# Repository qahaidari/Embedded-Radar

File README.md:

# Embedded-Radar-STMicrocontroller-Cprogramming
Embedded radar sensor circuit with STM32 microcontroller and C programming for measuring target speed

# Skills learned in this project:
* GIT
* Basics of hardware design and PCB layout
* Digital and analog circuits
* Accessing peripheral components
* Interrupts, serial I/O, general purpose I/O, ...
* RTOS, multitasking, synchronization, semaphores
* STM32CubeMx configuration code generator
* Schematic CAD software (KiCAD Eeschema): placing parts, connections in schematic, footprints, annotation, netlist
* PCB CAD software (KiCAD): loading netlist, GND pours, Vias, Gerber and Drill files for production
* Soldering components on PCB
* IDE Atollic TrueSTUDIO (Eclipse)
* C programming
* Configuring switches as external interrupts
* Communication between Interrupt Service Routine (ISR) and queue
* Configuring and using ADC
* Configuring and using timers
* Configuring LEDs
* Interfacing with LCD

# Project Description

## Introduction

RADAR stands for Radio Detection And Ranging and is a detection system that uses radio waves to determine the range, angle, or velocity of objects. It can be used to detect aircraft, ships, spacecraft, guided missiles, motor vehicles, weather formations, and terrain. Radars are now involved in various applications. It was initially used for target detection in military applications but nowadays it is used in tracking of aircrafts and vehicles and also in traffic control and space. In this project we will concentrate on motion and speed detection of objects using Radars.

The basic concept of Radar is sending an electromagnetic signal from a source which is radiating in the space. This signal will hit a moving object and then be reflected back to the source. In our case, the transmitter and receiver are on the same board of the radar device. The reflected signal from the object will be processed in the device and then finally sent to a microcontroller where the speed of the moving object is calculated using the Doppler effect.

The Doppler effect is the change of the frequency of an incident wave on a moving object in its reflected wave. The difference in frequencies is measured through a microcontroller to measure the speed of the moving object using the below formulas:

where  is the difference between transmitted and received frequencies of the signal,  is the wavelength,  is the frequency of the transmitted signal,  is the speed of light and  is the velocity of the object.

## Hardware Setup

### Circuit Design and Components

In this project, we are using an input source for the signal generation and reception, an amplifier and filter stage, a processing unit, a display, two switches and three LEDs. Below figure shows the block diagram of the project.

In the first stage, we use an IPM-165 Radar module which contains a full duplex patch antenna that transmits and receives signals in the K-band (24GHz). The reflected signal from the moving object has a slightly different frequency than that of the transmitted signal. This difference can be detected by the internal oscillator and the mixer inside the Radar module.

In the next stage, we use an amplifier to amplify the received signal for a more precise measurement and in order to increase the ability to detect objects far from the Radar module.

Due to possible additional noise in the environment which would affect the measurements negatively, we have also included a Notch filter that can suppress the noise at a certain frequency. We have included a filter with a 100Hz frequency suppression as we might have neon light in the environment which would produce signals in this range. The drawback is that the respective speeds in the 100Hz frequency range will not be detected. So we are using both a filtered signal and a non-filtered signal in this project.   

In the next stage we use the STM32L476 microcontroller. It converts the analog signal from the Radar module to a digital signal for processing. By processing the sampled digital signal, the microcontroller calculates the signal frequency and the speed of the object using the Doppler formula. The results for both filtered and non-filtered signals will be displayed on the LCD for user reading.

Two switches (one for switching between the filtered and non-filtered signal and one for freezing the maximum speed on the LCD) and three LEDs (for indicating the filtered, non-filtered and freeze states) are used for user requests and status indication.

### Schematic and Hardware Considerations

There are some points that should be considered in the hardware design in addition to the previous main blocks. We will highlight them in this section as shown in the following schematics.

**Power Supply Decoupling Capacitors:** It is highly recommended to connect capacitors to the input DC power supply to minimize the ripples that can be formed due to a non-ideal source. The capacitors C14 to C16 are used at the biasing of operational amplifier, Radar sensor and LCD and the capacitors C12 and C13 are connected to the input power supply. Below figure shows the schematic of decoupling capacitors for main power supply and power supplies of LCD, radar sensor and operational amplifier.

**Operational Amplifier and Notch Filter:** In our design, we used 3 Op-amps, and for size reduction we used a compact IC MC33079 which has 4 Op-amps. The first 2 Op-amps (U1A and U1B) are used in the amplifier circuit stage. The last Op-amp (U1D) is used as a voltage follower to isolate the effect of the load (microcontroller) on the voltage of the connected RC filter at the input of the Op-amp. The Notch filter is used to suppress the effect of noise at 100Hz frequency. Below figure shows the operational amplifier and the Notch filter with their connectivity to the microcontroller. The non-filtered signal is fed to pin PC0 and the filtered signal to pin PC1.

**Switch Buttons:** We used 2 switch buttons that should be connected to a debouncing circuit containing resistors and capacitors so that their bouncing when being pressed is canceled. Below figure shows their connectivity with the microcontroller. We used the formula

to calculate the time , and from it we can calculate the resistor value  from

Taking the bouncing time of the switches as  and the value of capacitor as , we calculated  

<a href="https://www.codecogs.com/eqnedit.php?latex=\large&space;\tau&space;>=&space;2.7(ms)" target="_blank">=&space;2.7(ms)" title="\large \tau >= 2.7(ms)" /></a>

and this gave us

<a href="https://www.codecogs.com/eqnedit.php?latex=\large&space;R&space;>=&space;27(k\Omega)" target="_blank">=&space;27(k\Omega)" title="\large R >= 27(k\Omega)" /></a>

We finally chose the smallest E24 resistor for  and  as . 

Below figure shows the two switches connected to microcontroller.

**LED Indicators:** We used 3 red LEDs for status indication of the measuring process. We need a resistor at each LED to operate them at the desired intensity. According to the data sheet, the voltage drop was calculated using the Kirchoff's voltage law, and the resistors were calculated as .

### Operational Flowchart
 
Below figure represents the flowchart of the Radar operation.

In this project we have considered 2 scales for the calculation of speed: Kilometer per hour and meter per second, both are displayed on the screen. We can distinguish between filtered and non-filtered signals. The user can switch between them by using switch 2 and the respective speeds in kmh and m/s will be displayed on the LCD. Switch 1 is used to freeze the maximum speed which has been captured so far. LED1 will be ON to indicate the freeze state, and LED2 and LED3 will be ON to show if the filtered signal or the nonfiltered signal has been selected respectively.
 
## Software Concept

**Interrupts:** There are two switches (SW1 and SW2) which act as external interrupts. The following external interrupt callback function sends a specific flag to the queue depending on which one has been pressed.

In the main task, anytime the SW2 flag is received from the queue, a switch between measurements for filtered and non-filtered signal will happen. This is done by changing the value of a local variable `state` on each SW2-ISR to Task communication. Depending on the value of `state`, an appropriate channel of ADC which takes samples from either a filtered or a non-filtered signal is selected.

**Global Variables:** The following global variables with their respective initial values have been used in the program:

```c 
int final_count = 0;
```
`final_count` indicates number of samples between two successive zeros in the signal.

```c
int timer_div = 0;
```
```c
int sample = 0, prevsample = 0;
```
```c
sample_count = 0;
```
`sample_count` is incremented each time a new sample is taken.

```c
freeze = 1;
```
```c
double min_final_count = 30000;
```

**Timer Settings for ADC Sampling:** The timer parameters have been set as the following:

```c
Prescaler = 1500;
```
```c
Period = 1;
```
```c
ClockDivision = 4;
```
Since the internal clock for the timer is 80MHz, these settings will make the final timer clock around 13333Hz. During each timer clock, ADC takes a sample and converts it to a digital value. This makes the sampling rate over 20 times the highest frequency (600Hz) in the received signal (Nyquist criterion for sampling an analog signal with at least twice the highest frequency in the signal has been fulfilled).

**Local Variables in the Default Task:**
```c
int cIn = 0;
```
```c
int state = 1;
```
```c
double half_period = 0, doppler_f = 0;
```
```c
double v_kmh = 0, v_ms = 0;
```
```c
char str[10];
```

**Static Local Variable:** The static local variable `OFFSET` is used in the timer service routine function to account for the offset value of the received signal.

**Communication between Timer Service Routine Function and the Task:**

Sending the flag `cIn = 3` from the timer SR to the queue: It is sent to the queue whenever a new zero crossing is detected and the current value of `sample_count` is put into `final_count` indicating the number of samples for the previous half period of the signal. `sample_count` value is then set to zero to start counting the number of samples in a new zero-crossing to zero-crossing interval.

The flag `cIn = 4` is sent to the queue whenever the global variable `timer_div` reaches 4000. `timer_div` is incremented any time a timer clock calls the timer service routine function in which a new sample is taken and counted. This flag is used in order not to refresh the contents on the LCD screen any time a new speed is about to be displayed.

**Functions of Switches and LEDs:**

SW2: Switching between filtered and non-filtered measurements

SW1: Freezing the max speed captured so far on LCD. The default state is not to freeze

LED2: Filtered signal has been selected

LED3: Non-filtered signal has been selected

LED1: Indicating the freeze state

**Freezing the Max Speed on LCD:** The global variable `min_final_count = 30000` is used in combination with the global variable `freeze` to freeze the maximum speed which has been captured so far. Switching between freezing and non-freezing states is done by the flag `cIn = 1` which is received in the default task from the EXTI Callback function.

Anytime a switch between filtered and non-filtered signal happens (through SW2), `min_final_count` is reset to 30000 so that the max speed for the new signal type will not be affected by the values of the last signal type. Also, if this switch happens in the freeze state, the speed values will be reset to zero so that the previous frozen max speeds will not stay on the LCD screen.

In the non-freeze state, whenever a new `final_count` is received (through timer SR to task communication), it is compared with the current `min_final_count` to update it for the max speed in the freeze state. In the freeze state, `min_final_count` is taken for measurements.

## Conclusion

**A Concluding Note on Frequency Calculation:** When a signal is received from the Radar sensor, the calculation will be performed in the processor of the microcontroller. Since the highest signal frequency that is received is 600Hz, the sampling rate according to the Nyquist criteria should be at least double this value. We have adjusted the timer parameters in such a way so that the timer service function is called 13333 times per second and within each call, ADC takes one sample. This makes the sampling rate over 20 times the highest frequency. Whenever one sample is taken, it is compared with its previous sample to detect two successive zero crossings and count the number of samples taken within these zero crossings. Since the time for taking one sample is known based on the sampling rate of the timer/ADC, the half period of the signal can be measured. During this process, an offset value and also a threshold value for canceling the noise have been considered. By knowing the period and frequency of the signal, the speed of the object will be measured using the Doppler formula. 

The user can hold the reading on the LCD screen if switch 1 is pressed which will display the maximum speed calculated since the last reading. LED1 will be on to indicate the hold state. The user can release the hold state by pressing switch 1 again and the system will return again to wait for a new received signal.

# Below figure shows the final PCB with soldered components, mounted on the STMicrocontroller.

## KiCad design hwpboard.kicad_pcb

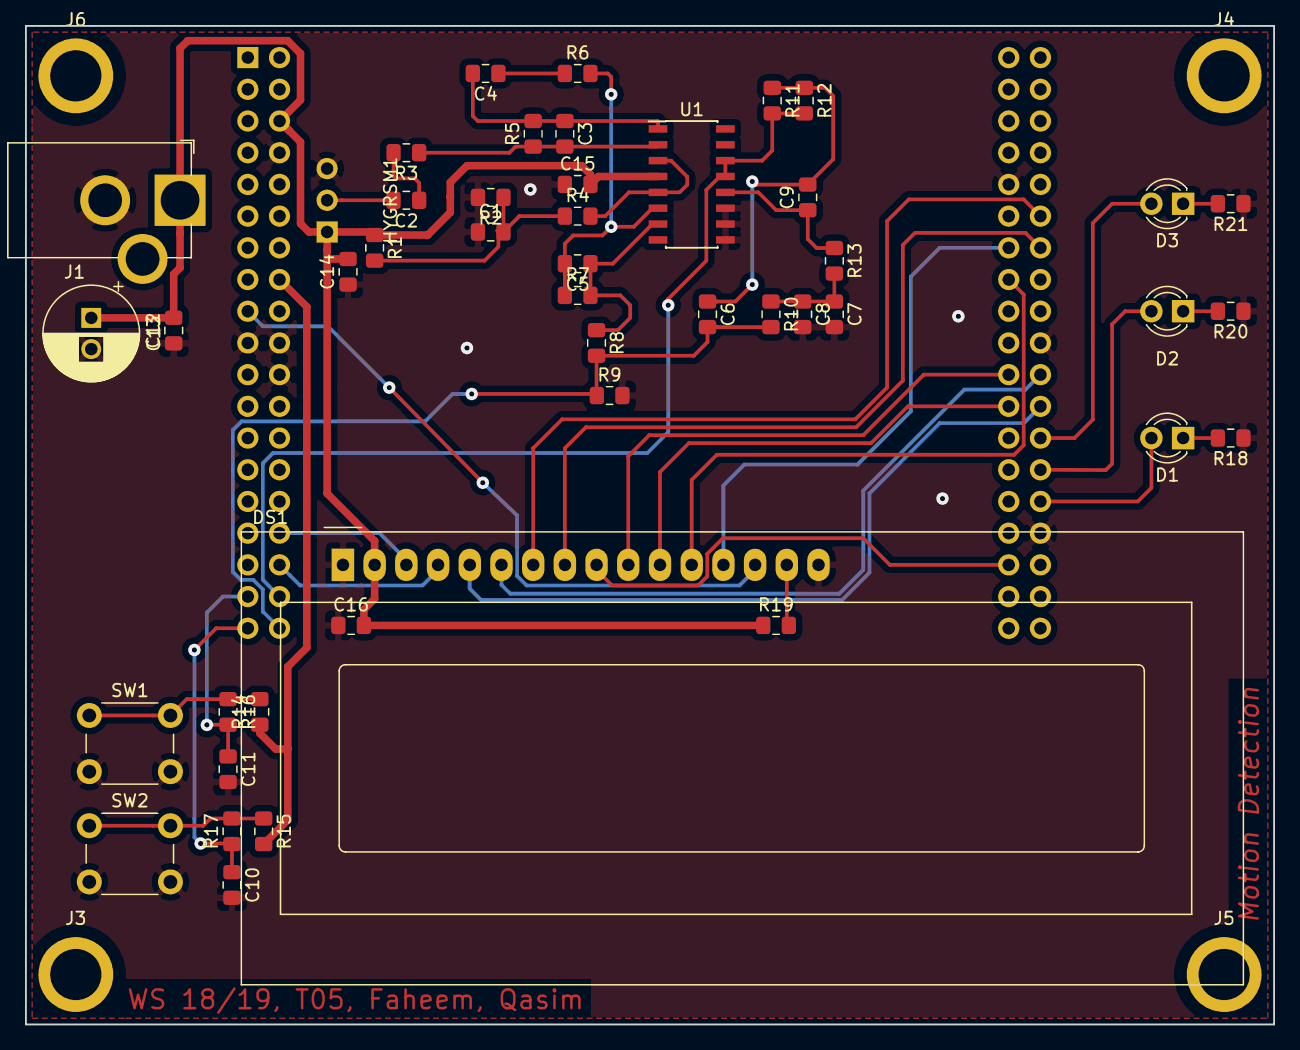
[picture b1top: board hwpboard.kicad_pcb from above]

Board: 2 copper layers, 100.0 x 80.0 mm, 51 parts (0 on the bottom side), 40 nets.

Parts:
C1, C2, C4: 10u; C_0805_2012Metric_Pad1.15x1.40mm_HandSolder
C3, C5: 1n; C_0805_2012Metric_Pad1.15x1.40mm_HandSolder
C6, C7, C8, C9: 33n; C_0805_2012Metric_Pad1.15x1.40mm_HandSolder
C10, C11, C12, C14, C15, C16: 100n; C_0805_2012Metric_Pad1.15x1.40mm_HandSolder
C13: 47u; CP_Radial_D7.5mm_P2.50mm
D1, D2, D3: RED; LED_D3.0mm
DS1: WC1602A; WC1602A_no_mount
HYGRSM1: HYG_RSM_1650; HYG_RSM-1650
J1: Barrel_Jack_Switch; BarrelJack_Horizontal_CustomHWP
J3, J4, J5, J6: Conn_01x01; MountingHole_4.1mm_M4_ISO14580_Pad
NUCBRD1: NUCLEO64; ST_Morpho_Connector_STLink
R1, R2: 10k; R_0805_2012Metric_Pad1.15x1.40mm_HandSolder
R3, R6: 4.7k; R_0805_2012Metric_Pad1.15x1.40mm_HandSolder
R4: 1k; R_0805_2012Metric_Pad1.15x1.40mm_HandSolder
R5, R7: 150k; R_0805_2012Metric_Pad1.15x1.40mm_HandSolder
R8: 300; R_0805_2012Metric_Pad1.15x1.40mm_HandSolder
R9: 2k; R_0805_2012Metric_Pad1.15x1.40mm_HandSolder
R10, R11, R12, R13, R14, R15: 47k; R_0805_2012Metric_Pad1.15x1.40mm_HandSolder
R16, R17: 30k; R_0805_2012Metric_Pad1.15x1.40mm_HandSolder
R18, R20, R21: 180; R_0805_2012Metric_Pad1.15x1.40mm_HandSolder
R19: 100; R_0805_2012Metric_Pad1.15x1.40mm_HandSolder
SW1, SW2: SW_Push; SW_PUSH_6mm
U1: MC33079; SOIC-16_3.9x9.9mm_P1.27mm

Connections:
+3V3: NUCBRD1.16, R14.1, R15.2
+5V: C12.2, C13.1, C14.2, C15.2, C16.2, DS1.2, HYGRSM1.1, J1.1, NUCBRD1.6, R1.1, R19.1, U1.4
GND: C1.1, C7.2, C8.2, C10.2, C11.2, C12.1, C13.2, C14.1, C15.1, C16.1, DS1.1, DS1.16, HYGRSM1.3, J1.2, NUCBRD1.8, NUCBRD1.19, NUCBRD1.20, NUCBRD1.22, NUCBRD1.47, NUCBRD1.58, NUCBRD1.70, R2.2, R9.2, R18.1, R20.1, R21.1, SW1.2, SW2.2, U1.9, U1.10, U1.11
LCD_D7: DS1.14, NUCBRD1.17
LCD_V0: DS1.3, NUCBRD1.32
unnamed: C1.2, R1.2, R2.1, R4.1
unnamed: C2.1, R3.2
unnamed: C2.2, HYGRSM1.2
unnamed: C3.1, C4.2, R5.2, U1.1
unnamed: C3.2, R3.1, R5.1, U1.2
unnamed: C4.1, R6.1
unnamed: C5.1, R7.2, R8.1, U1.7
unnamed: C5.2, R6.2, R7.1, U1.6
unnamed: C6.1, C9.2, R11.1, R12.1
unnamed: C7.1, C8.1, R10.1, R13.2
unnamed: C9.1, R13.1, U1.12
unnamed: C10.1, NUCBRD1.37, R17.1
unnamed: C11.1, NUCBRD1.35, R16.2
unnamed: D1.1, R18.2
unnamed: D1.2, NUCBRD1.68
unnamed: D2.1, R20.2
unnamed: D2.2, NUCBRD1.66
unnamed: D3.1, R21.2
unnamed: D3.2, NUCBRD1.64
unnamed: DS1.4, NUCBRD1.34
unnamed: DS1.5, NUCBRD1.62
unnamed: DS1.6, NUCBRD1.60
unnamed: DS1.7, NUCBRD1.50
unnamed: DS1.8, NUCBRD1.52
unnamed: DS1.9, NUCBRD1.71
unnamed: DS1.10, NUCBRD1.59
unnamed: DS1.11, NUCBRD1.61
unnamed: DS1.12, NUCBRD1.53
unnamed: DS1.13, NUCBRD1.51
unnamed: DS1.15, R19.2
unnamed: NUCBRD1.36, R11.2, R12.2, U1.13, U1.14
unnamed: R4.2, U1.3, U1.5
unnamed: R14.2, R16.1, SW1.1
unnamed: R15.1, R17.2, SW2.1
Sig_unfiltered: C6.2, NUCBRD1.38, R8.2, R9.1, R10.2

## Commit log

2020-11-18 Create Block_diagram
